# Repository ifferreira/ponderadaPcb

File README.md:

# Placa de circuito impresso com Raspberry Pi Pico

Disposição geral do repositório, com os diretórios e seus respectivos arquivos:
```
│   README.md
│
├───src
│       fp-info-cache
│       ponderadaPcb-B_Cu.gbr
│       ponderadaPcb-B_Mask.gbr
│       ponderadaPcb-B_Paste.gbr
│       ponderadaPcb-B_Silkscreen.gbr
│       ponderadaPcb-Edge_Cuts.gbr
│       ponderadaPcb-F_Cu.gbr
│       ponderadaPcb-F_Mask.gbr
│       ponderadaPcb-F_Paste.gbr
│       ponderadaPcb-F_Silkscreen.gbr
│       ponderadaPcb-job.gbrjob
│       ponderadaPcb.kicad_pcb
│       ponderadaPcb.kicad_prl
│       ponderadaPcb.kicad_pro
│       ponderadaPcb.kicad_sch
│       ~ponderadaPcb.kicad_sch.lck
│
└───static
    └───img
            3d.png
            esquematico.png
            pcb.png
```

Dentro do diretório "src", há alguns arquivos importantes para considerar, a saber:
1. gbr: arquivos com essa terminação se referem aos arquivos Gerber, que são importantíssimos arquivos para a fabricação de PCB, pois descrevem os vários elementos e constituintes da placa de circuito impresso;
2. kicad_pcb: o arquivo com essa terminação se refere ao design da PCB;
3. kicad_pro: o arquivo com essa terminação se refere ao design final do projeto;
4. kicad_sch: o arquivo com essa terminação se refere ao esquemático da PCB.

O projeto contou com os seguintes componentes:
- Raspberry Pi Pico;
- Trasnsistor;
- LED;
- Resistor.

A seguir, imagens do esquemático, do design PCB e da visualização 3D, respectivamente:

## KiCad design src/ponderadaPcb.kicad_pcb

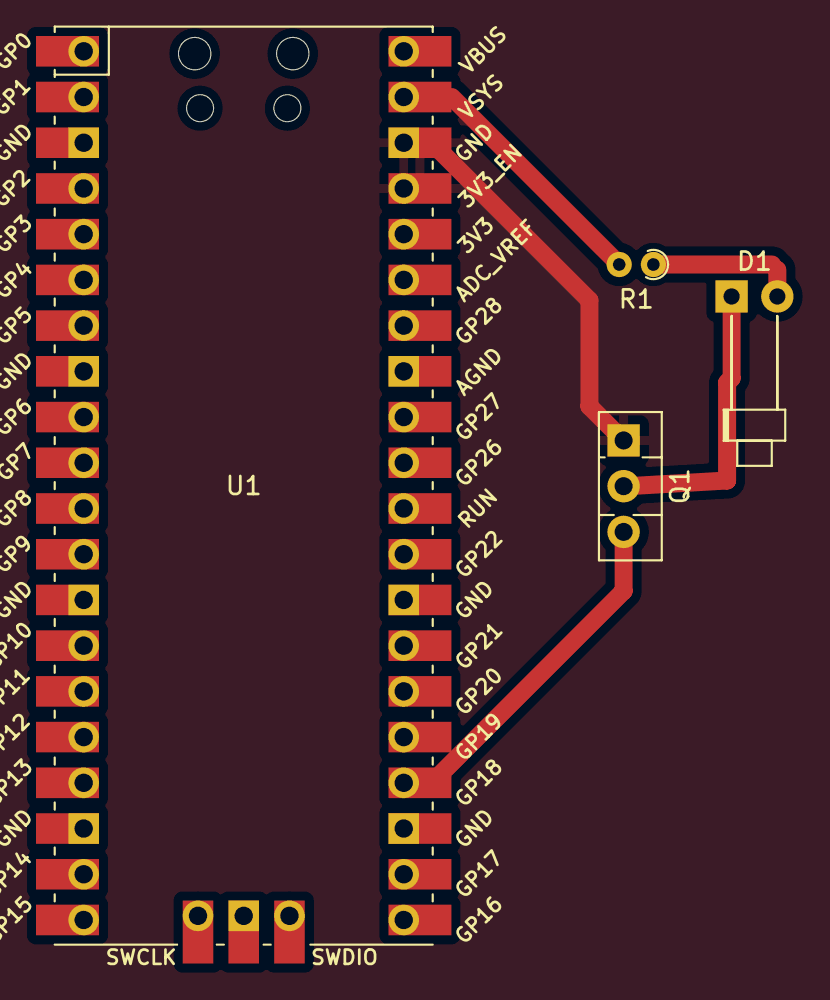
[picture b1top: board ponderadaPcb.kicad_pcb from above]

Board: 2 copper layers, 4 parts (0 on the bottom side), 5 nets.

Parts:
D1: LED; LED_D1.8mm_W1.8mm_H2.4mm_Horizontal_O6.35mm_Z8.2mm
Q1: BF457; TO-126-3_Vertical
R1: R; R_Axial_DIN0204_L3.6mm_D1.6mm_P1.90mm_Vertical
U1: Pico; RPi_Pico_SMD_TH

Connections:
GND: Q1.1 (E), U1.37 (3V3_EN), U1.38 (GND)
unnamed: D1.2 (A), R1.1
unnamed: D1.1 (K), Q1.2 (C)
unnamed: Q1.3 (B), U1.24 (GPIO18), U1.25 (GPIO19)
VCC: R1.2, U1.39 (VSYS)

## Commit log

2024-03-27 add esquemático e pcb
2024-03-31 update esquematico
2024-03-31 update readme and esquematico
